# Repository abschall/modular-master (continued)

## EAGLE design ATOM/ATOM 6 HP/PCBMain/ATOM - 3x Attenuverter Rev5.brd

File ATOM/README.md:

# ATOM - ATtenuverter Offset Mixer 

<div align="justify">
  
ATOM is a three channel ATtenuverter and Offset Mixer. Each input is equipped with a dedicated bipolar control potentiometer for its input. When a cable is plugged into an input jack, the corresponding channel's potentiometer acts as an attenuverter.

In the absence of an input signal (no cable patched to an input), the input automatically normalizes to a 5V DC offset. The dedicated potentiometer then adjusts the offset voltage from -5V (fully counterclockwise) to +5V DC (fully clockwise), with a neutral 0V DC offset at the 12 o'clock position. Each channel combines inputs A and B, providing the summed output at the OUT jack. Should no cable be connected to a channel's OUT jack, its output is cascaded to the next channel, allowing ATOM to function as a versatile mixer with configurations of 2, 4, or even 6 channels, depending on how the outputs are utilized and connected.
The project is available in two formats: a smaller 6 HP version and a more performance-oriented 10HP version, catering to different preferences and potentially accommodating those with larger fingers.
</div>

_Status:_

March 2024: Publication of the project.  
ATOM 6 HP : Revision 5 (02/2022)  
ATOM large 10 HP: Revision 6 (03 / 2024)

_License:_  

This work is licensed under [CC BY-SA 4.0]. (https://creativecommons.org/licenses/by-sa/4.0/)

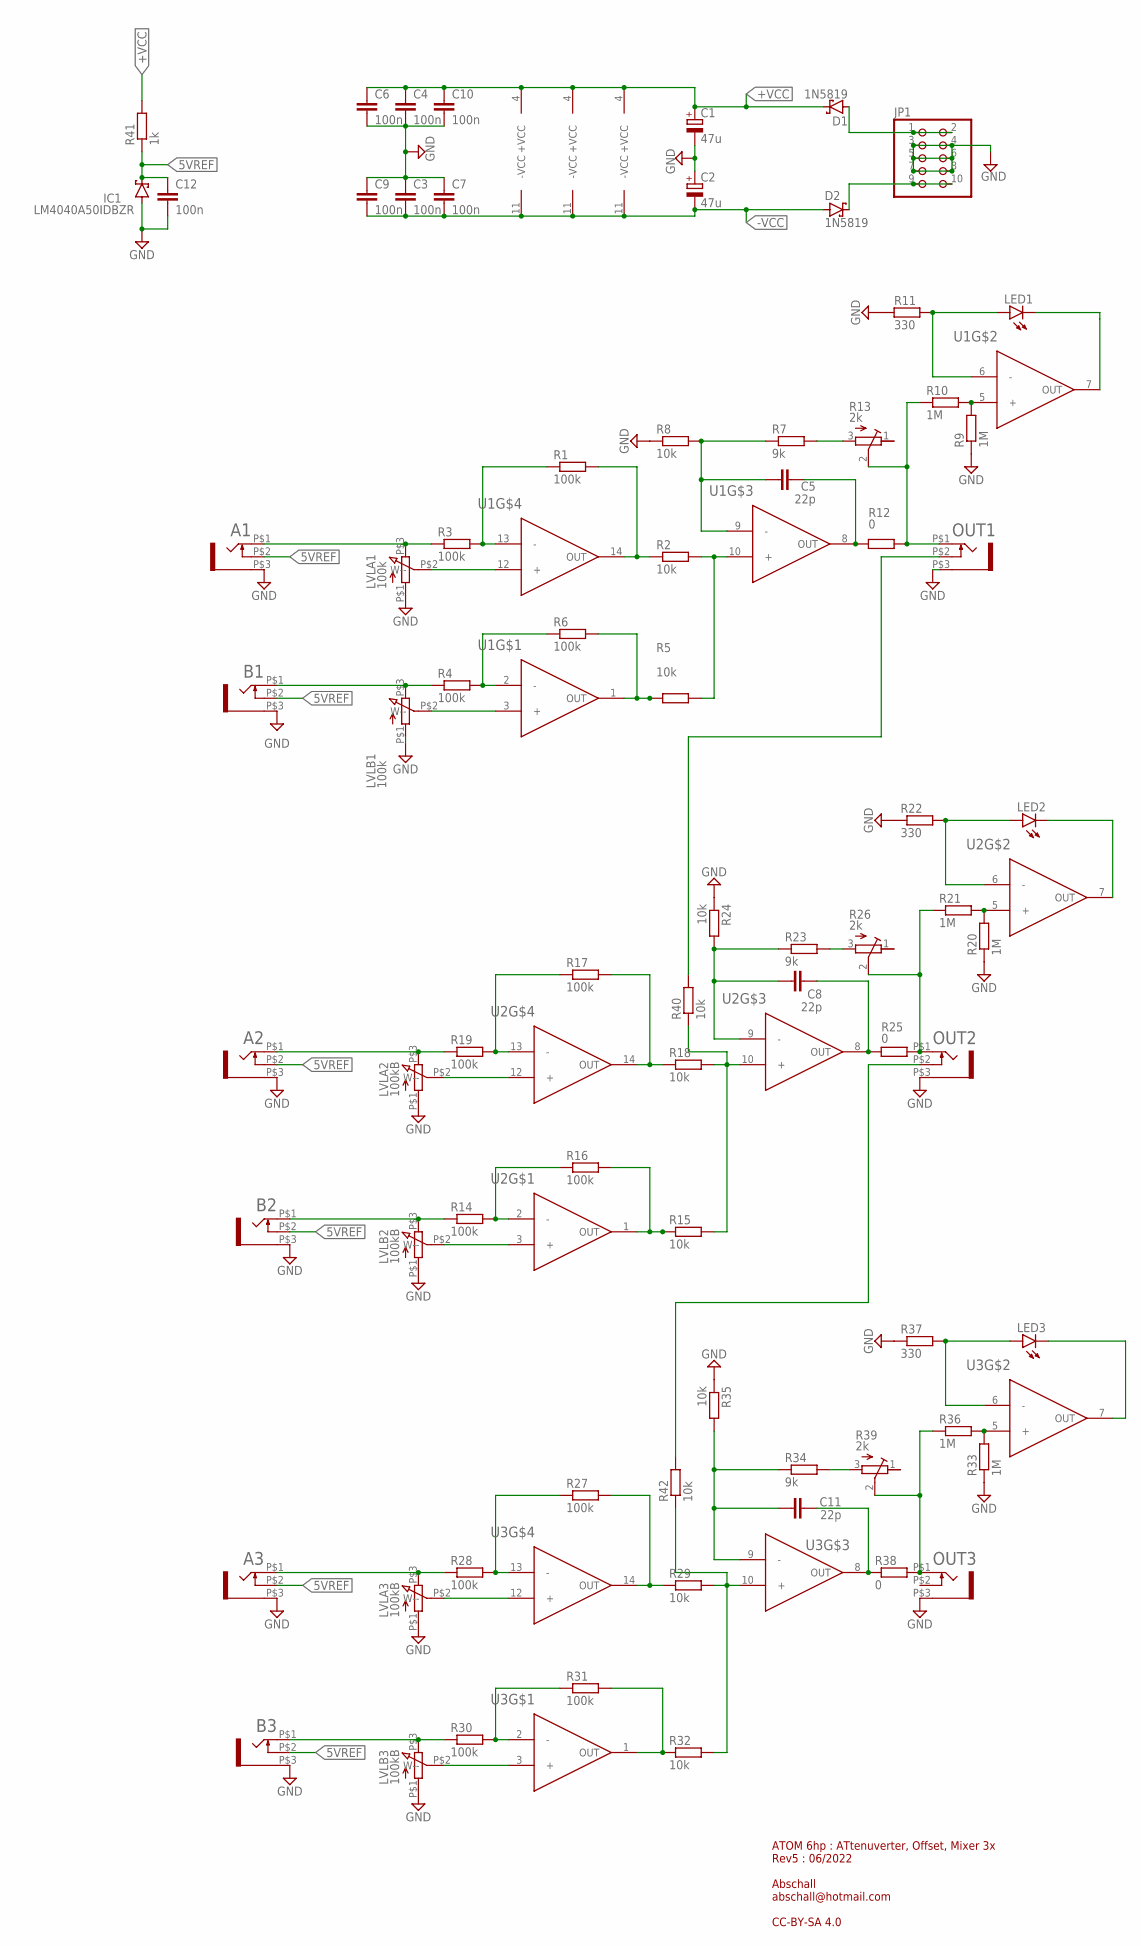
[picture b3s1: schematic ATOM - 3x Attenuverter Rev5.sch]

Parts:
A1, A2, A3: WQP-PJ301M-12_JACK
B1, B2, B3: WQP-PJ301M-12_JACK
C1, C2: 47u; PANASONIC_B
C3, C4, C6, C7, C9, C10, C12: 100n; C0805
C5, C8, C11: 22p; C0805
D1, D2: 1N5819; SOD123
IC1: LM4040A50IDBZR; SOT23
JP1: PINHD-2X5; 2X05
LED1, LED2, LED3: LED3MM
LVLA1: 100k; ALPHA9MM
LVLA2, LVLA3: 100kB; ALPHA9MM
LVLB1: 100k; ALPHA9MM
LVLB2, LVLB3: 100kB; ALPHA9MM
OUT1, OUT2, OUT3: WQP-PJ301M-12_JACK
R1, R3, R4, R6, R14, R16, R17, R19, R27, R28, R30, R31: 100k; R0805
R2, R5, R8, R15, R18, R24, R29, R32, R35, R40, R42: 10k; R0805
R7, R23, R34: 9k; R0805
R9, R10, R20, R21, R33, R36: 1M; R0805
R11, R22, R37: 330; R0805
R12, R25, R38: 0; R0805
R13, R26, R39: 2k; RTRIM3314J
R41: 1k; R0805
U1, U2, U3: TL74H; SO14

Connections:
5VREF: A1.P$2 (3), A2.P$2 (3), A3.P$2 (3), B1.P$2 (3), B2.P$2 (3), B3.P$2 (3), C12.1, IC1.1 (C), R41.1
+VCC: C1.+, C4.1, C6.1, C10.1, D1.C, R41.2, U1.4 (+VCC), U2.4 (+VCC), U3.4 (+VCC)
-VCC: C2.-, C3.2, C7.2, C9.2, D2.A, U1.11 (-VCC), U2.11 (-VCC), U3.11 (-VCC)
GND: A1.P$3 (1), A2.P$3 (1), A3.P$3 (1), B1.P$3 (1), B2.P$3 (1), B3.P$3 (1), C1.-, C2.+, C3.1, C4.2, C6.2, C7.1, C9.1, C10.2, C12.2, IC1.2 (A), JP1.3, JP1.4, JP1.5, JP1.6, JP1.7, JP1.8, LVLA1.P$1 (1), LVLA2.P$1 (1), LVLA3.P$1 (1), LVLB1.P$1 (1), LVLB2.P$1 (1), LVLB3.P$1 (1), OUT1.P$3 (1), OUT2.P$3 (1), OUT3.P$3 (1), R8.1, R9.1, R11.1, R20.1, R22.1, R24.1, R33.1, R35.1, R37.1
unnamed: A1.P$1 (2), LVLA1.P$3 (3), R3.1
unnamed: R1.1, R3.2, U1.13 (-)
unnamed: LVLB1.P$2 (W--), U1.3 (+)
unnamed: R1.2, R2.1, U1.14 (OUT)
unnamed: R2.2, R5.2, U1.10 (+)
unnamed: R5.1, R6.2, U1.1 (OUT)
unnamed: R4.2, R6.1, U1.2 (-)
unnamed: B1.P$1 (2), LVLB1.P$3 (3), R4.1
unnamed: C5.1, R7.1, R8.2, U1.9 (-)
unnamed: OUT1.P$1 (2), R10.1, R12.2, R13.2 (S)
unnamed: LED1.A, R11.2, U1.6 (-)
unnamed: LED1.K (C), U1.7 (OUT)
unnamed: R9.2, R10.2, U1.5 (+)
unnamed: A2.P$1 (2), LVLA2.P$3 (3), R19.1
unnamed: LVLA1.P$2 (W--), U1.12 (+)
unnamed: R17.1, R19.2, U2.13 (-)
unnamed: R17.2, R18.1, U2.14 (OUT)
unnamed: R15.2, R18.2, R40.1, U2.10 (+)
unnamed: R14.2, R16.1, U2.2 (-)
unnamed: C8.1, R23.1, R24.2, U2.9 (-)
unnamed: B2.P$1 (2), LVLB2.P$3 (3), R14.1
unnamed: OUT2.P$1 (2), R21.1, R25.2, R26.2 (S)
unnamed: LED2.A, R22.2, U2.6 (-)
unnamed: LED2.K (C), U2.7 (OUT)
unnamed: R20.2, R21.2, U2.5 (+)
unnamed: R15.1, R16.2, U2.1 (OUT)
unnamed: LVLA2.P$2 (W--), U2.12 (+)
unnamed: A3.P$1 (2), LVLA3.P$3 (3), R28.1
unnamed: LVLB2.P$2 (W--), U2.3 (+)
unnamed: R27.1, R28.2, U3.13 (-)
unnamed: R27.2, R29.1, U3.14 (OUT)
unnamed: R29.2, R32.2, R42.1, U3.10 (+)
unnamed: R30.2, R31.1, U3.2 (-)
unnamed: C11.1, R34.1, R35.2, U3.9 (-)
unnamed: B3.P$1 (2), LVLB3.P$3 (3), R30.1
unnamed: R23.2, R26.3 (A)
unnamed: LED3.A, R37.2, U3.6 (-)
unnamed: LED3.K (C), U3.7 (OUT)
unnamed: R33.2, R36.2, U3.5 (+)
unnamed: R31.2, R32.1, U3.1 (OUT)
unnamed: LVLA3.P$2 (W--), U3.12 (+)
unnamed: D2.C, JP1.9, JP1.10
unnamed: D1.A, JP1.1, JP1.2
unnamed: LVLB3.P$2 (W--), U3.3 (+)
unnamed: C5.2, R12.1, U1.8 (OUT)
unnamed: C8.2, R25.1, U2.8 (OUT)
unnamed: C11.2, R38.1, U3.8 (OUT)
unnamed: OUT2.P$2 (3), R42.2
unnamed: OUT1.P$2 (3), R40.2
unnamed: OUT3.P$1 (2), R36.1, R38.2, R39.2 (S)
unnamed: R7.2, R13.3 (A)
unnamed: R34.2, R39.3 (A)

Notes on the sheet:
ATOM 6hp : ATtenuverter, Offset, Mixer 3x Rev5 : 06/2022 Abschall abschall@hotmail.com CC-BY-SA 4.0

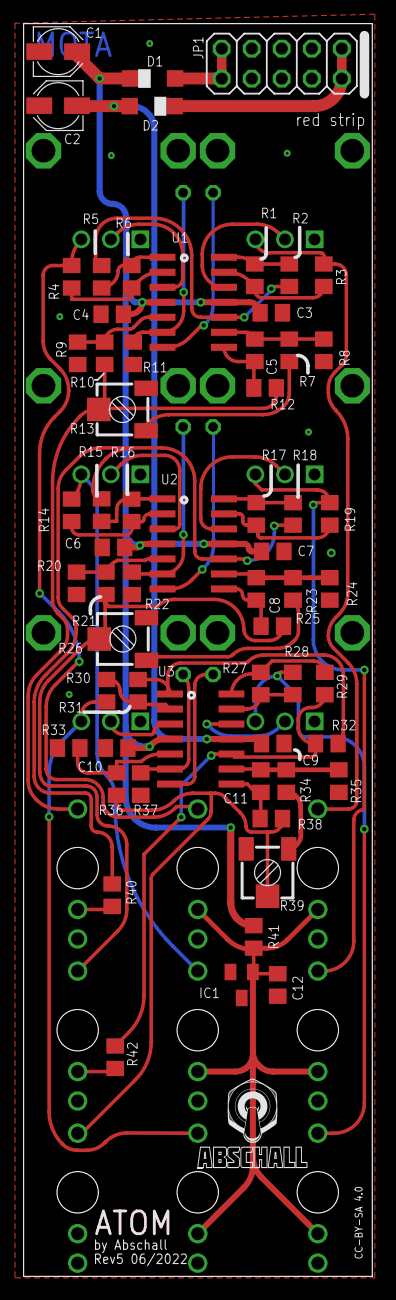
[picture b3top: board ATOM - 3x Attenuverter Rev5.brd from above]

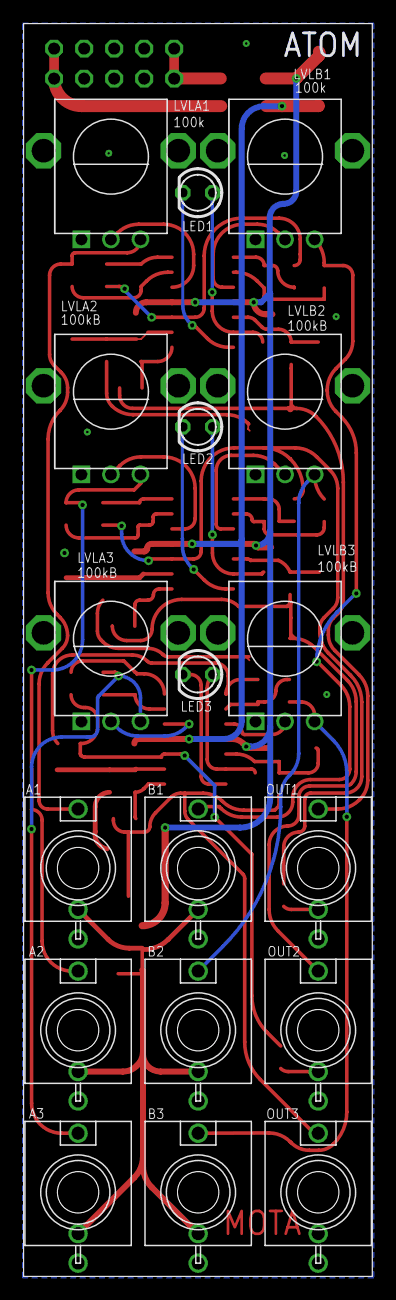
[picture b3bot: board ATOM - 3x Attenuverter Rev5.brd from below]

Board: 2 copper layers, 29.5 x 106.0 mm, 79 parts (18 on the bottom side), 56 nets.

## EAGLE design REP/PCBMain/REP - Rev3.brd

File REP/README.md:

# REP -  Audio Buffered Mults 

<div align="justify">
REP is a two channel 1-in-3 Audio Buffered Multiple (or Mults). Input signals applied to the input sockets (sockets marked and ) are replicated at the three output sockets directly below. Each output is buffered using NE5532 dual Operational Amplifiers for audio signal integrity. 
In scenarios where no input is connected to the second channel, the first channel is automatically normalled to the second channel. Consequently, the module functions as a 1-in-6 buffered multiple, effectively distributing the input signal across six outputs.    
  
</div>  
<br/>
<br/>

_Status:_ 

March 2024: Publication of the project.  
REP: Revision 3 (10/2021)
<br/>
<br/>
_License:_<br/>
This work is licensed under [CC BY-SA 4.0]. (https://creativecommons.org/licenses/by-sa/4.0/)

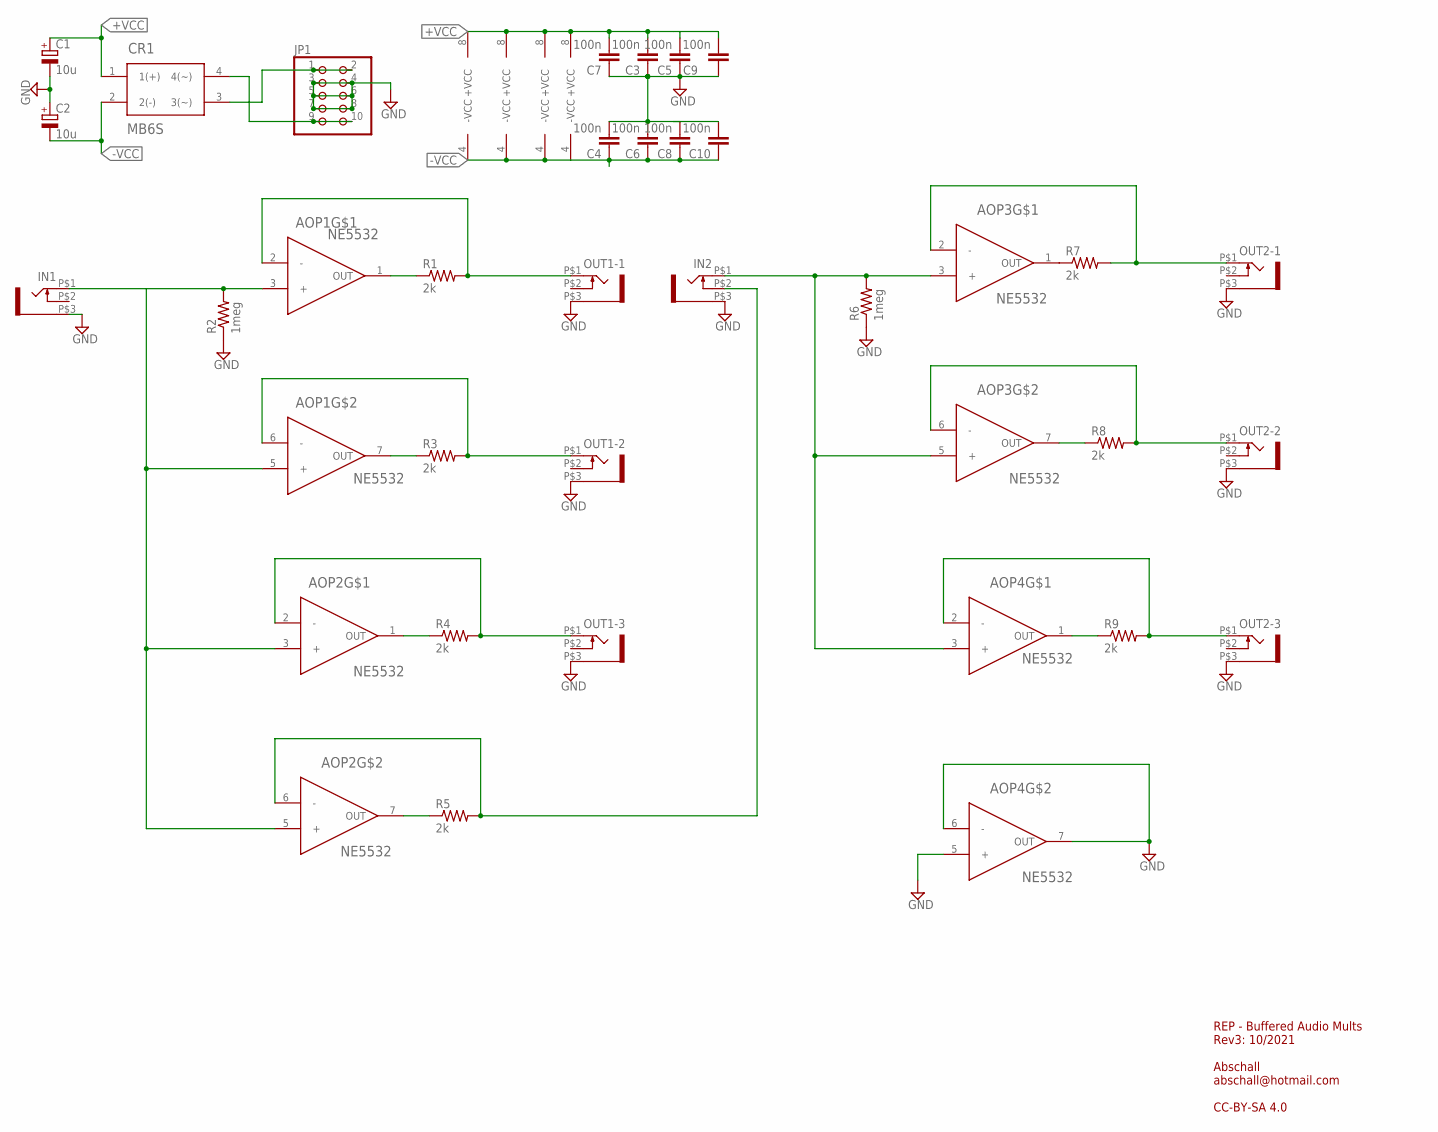
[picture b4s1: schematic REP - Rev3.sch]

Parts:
AOP1, AOP2, AOP3, AOP4: NE5532; SOIC8
C1, C2: 10u; PANASONIC_B
C3, C4, C5, C6, C7, C8, C9, C10: 100n; C0805
CR1: MB6S; 4SOIC
IN1, IN2: WQP-PJ301M-12_JACK
JP1: PINHD-2X5; 2X05
OUT1-1, OUT1-2, OUT1-3, OUT2-1, OUT2-2, OUT2-3: WQP-PJ301M-12_JACK
R1, R3, R4, R5, R7, R8, R9: 2k; R0805
R2, R6: 1meg; R0805

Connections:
+VCC: AOP1.8 (+VCC), AOP2.8 (+VCC), AOP3.8 (+VCC), AOP4.8 (+VCC), C1.+, C3.2, C5.2, C7.2, C9.2, CR1.1 (1(+))
-VCC: AOP1.4 (-VCC), AOP2.4 (-VCC), AOP3.4 (-VCC), AOP4.4 (-VCC), C2.-, C4.1, C6.1, C8.1, C10.1, CR1.2 (2(-))
GND: AOP4.5 (+), AOP4.6 (-), AOP4.7 (OUT), C1.-, C2.+, C3.1, C4.2, C5.1, C6.2, C7.1, C8.2, C9.1, IN1.P$3 (1), IN2.P$3 (1), JP1.3, JP1.4, JP1.5, JP1.6, JP1.7, JP1.8, OUT1-1.P$3 (1), OUT1-2.P$3 (1), OUT1-3.P$3 (1), OUT2-1.P$3 (1), OUT2-2.P$3 (1), OUT2-3.P$3 (1), R2.1, R6.1
unnamed: AOP1.2 (-), OUT1-1.P$1 (2), R1.2
unnamed: AOP1.6 (-), OUT1-2.P$1 (2), R3.2
unnamed: AOP1.1 (OUT), R1.1
unnamed: AOP1.7 (OUT), R3.1
unnamed: CR1.3 (3(~)), JP1.1, JP1.2
unnamed: AOP1.3 (+), AOP1.5 (+), AOP2.3 (+), AOP2.5 (+), IN1.P$1 (2), R2.2
unnamed: AOP3.2 (-), OUT2-1.P$1 (2), R7.2
unnamed: AOP2.1 (OUT), R4.1
unnamed: AOP3.6 (-), OUT2-2.P$1 (2), R8.2
unnamed: AOP3.1 (OUT), R7.1
unnamed: AOP3.7 (OUT), R8.1
unnamed: AOP4.2 (-), OUT2-3.P$1 (2), R9.2
unnamed: AOP4.1 (OUT), R9.1
unnamed: AOP3.3 (+), AOP3.5 (+), AOP4.3 (+), IN2.P$1 (2), R6.2
unnamed: AOP2.7 (OUT), R5.1
unnamed: AOP2.2 (-), OUT1-3.P$1 (2), R4.2
unnamed: AOP2.6 (-), IN2.P$2 (3), R5.2
unnamed: CR1.4 (4(~)), JP1.9, JP1.10

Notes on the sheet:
REP - Buffered Audio Mults Rev3: 10/2021 Abschall abschall@hotmail.com CC-BY-SA 4.0

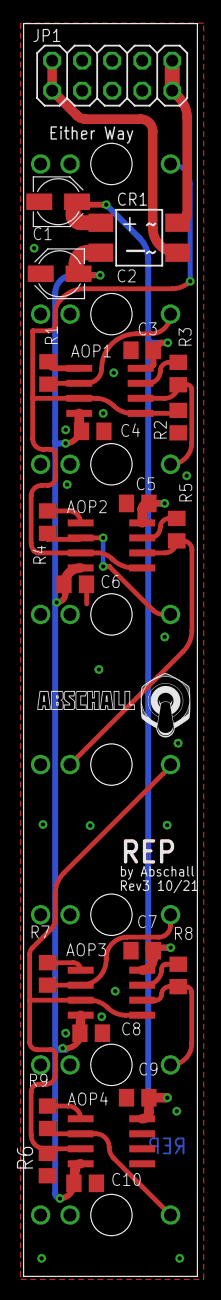
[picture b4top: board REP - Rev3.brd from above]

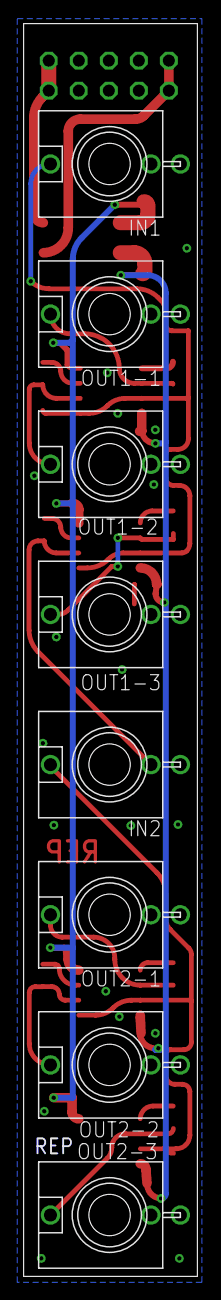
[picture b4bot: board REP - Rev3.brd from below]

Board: 2 copper layers, 14.7 x 106.0 mm, 33 parts (8 on the bottom side), 21 nets.

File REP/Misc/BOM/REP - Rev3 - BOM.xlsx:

REP - Rev 2 - BOM
Qty | Value | Package | Parts | Description | Mouser Ref | Cart | Bought | Built
Resistors
7 | 2k | R0805 | R1, R3,R4, R5, R7, R8, R9 | RESISTOR 1%
2 | 1meg | R0805 | R2, R6 | RESISTOR 1%
Capacitors
8 | 100n | C0805 | C3, C4, C5, C6, C7, C8, C9, C10 | CAPACITOR
2 | 10u | PANASONIC_B | C1, C2 | POLARIZED CAPACITOR | 667-EEE-HBC220UAR
Ics
1 | MB6S | 4SOIC | CR1 | BRIDGE RECTIFIER | 512-MB6S | PCBLayout.com
4 | NE5532 | SOIC8 | AOP1, AOP2, AOP3, AOP4 | Dual Opamp | 595-NE5532DR
Through Hole Stuff
1 | 2X5 Male Pin Header | 2X5 Male Pin Header | JP1 | PIN HEADER |  | TAYDA
8 | PJ301M | WQP-PJ301M-12_JACK | IN1, IN2, OUT1-1, OUT1-2, OUT1-3, OUT2-1, OUT2-2, OUT2-3 |  |  | https://www.thonk.co.uk/shop/thonkiconn/

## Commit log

2024-03-27 Initial commit
    created a new "modular-master" repository. This respository should contain only major commits, major changes and new publications.
2024-03-27 Side Brackets : published project
    3D printed Side Brackets for 3U eurorack Type 1 rails
2024-03-27 REP: published project
    REP is a 2 channel audio buffered multiple.
    The project is published under licence : CC BY-SA 4.0
    Panel .brd file is not provided.
2024-03-27 ATOM: published project
    ATOM is a three channel Attenuverter Offset and Mixer. It is declined in two versions, a smaller 6 HP version and a 10 HP version.
    Project is published under licence CA BY-SA 4.0
    Panels .brd files are not provided.
2024-03-28 REP & ATOM: replaced some pictures, added ibom
    - added clearer pictures of the front and back of ATOM
    - added picture of front of REP
    - added iBom for ATOM 6HP, ATOM 10HP and REP
2024-04-01 2xVCA: published project
    2x VCA is a two-channel VCA based on Mutable Instruments' Veils, designed by Émilie Gillet.
    A blank Panel is provided in the \Panel sub-folder.
2024-04-02 MOUNTS: added (non-released) project to proto-branch
    - untested prototype.
    - missing panel design.
